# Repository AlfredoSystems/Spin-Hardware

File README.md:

# Spin-Hardware
Control system PCB files for The Greatest Danger and The Greatest Challenge. This Repo includes KiCAD projects for two boards, "Spin-Sonic" and "Spin-Eggman". "Spin-Sonic" is the main control board with RF, sensing, and the main MCU. "Spin-Eggman" is a power distribution board used to compactly mount the main switch, bulk capacitors, and battery connectors.

> ⚠️ While it's cool with us, I don't recommend anyone reproduce these exact boards. Learn more at the bottom of this page.

## Spin-Sonic Features
* Main MCU STM32F405RGT6 has FPU and high clock speed.
* 400g H3LIS331DL Accelerometer is rotated 45 degrees for increased precision.
* SX1276 915MHz LoRa transceiver circuit provides reliable wireless communication.
* SY8253ADC switching regulator provides up to 3A at 3.3V. Maximum input voltage of 23V. 
* TRRS jack provides swift and robust Serial Wire Debug (SWD) programming interface

## Why you shouldn't make one of these
1. The LoRa wireless system is put together pretty much from scratch. They don't really sell handheld LoRa transmitters. We made one ourselves, a process I do not recommend to anyone. We also have to make the antenna for each board.
2. Spin-Sonic was designed to be assembled by JLCPCB, unfortunately JLC does not stock 400g accelerometers. H3LIS331DL's had to be soldered after the fact, a process that can be tedious and unreliable.
3. Using a TRRS connector (audio jack) for the programming interface does make rapid code testing easier, but we did have to make a custom programming cable which was a pain.

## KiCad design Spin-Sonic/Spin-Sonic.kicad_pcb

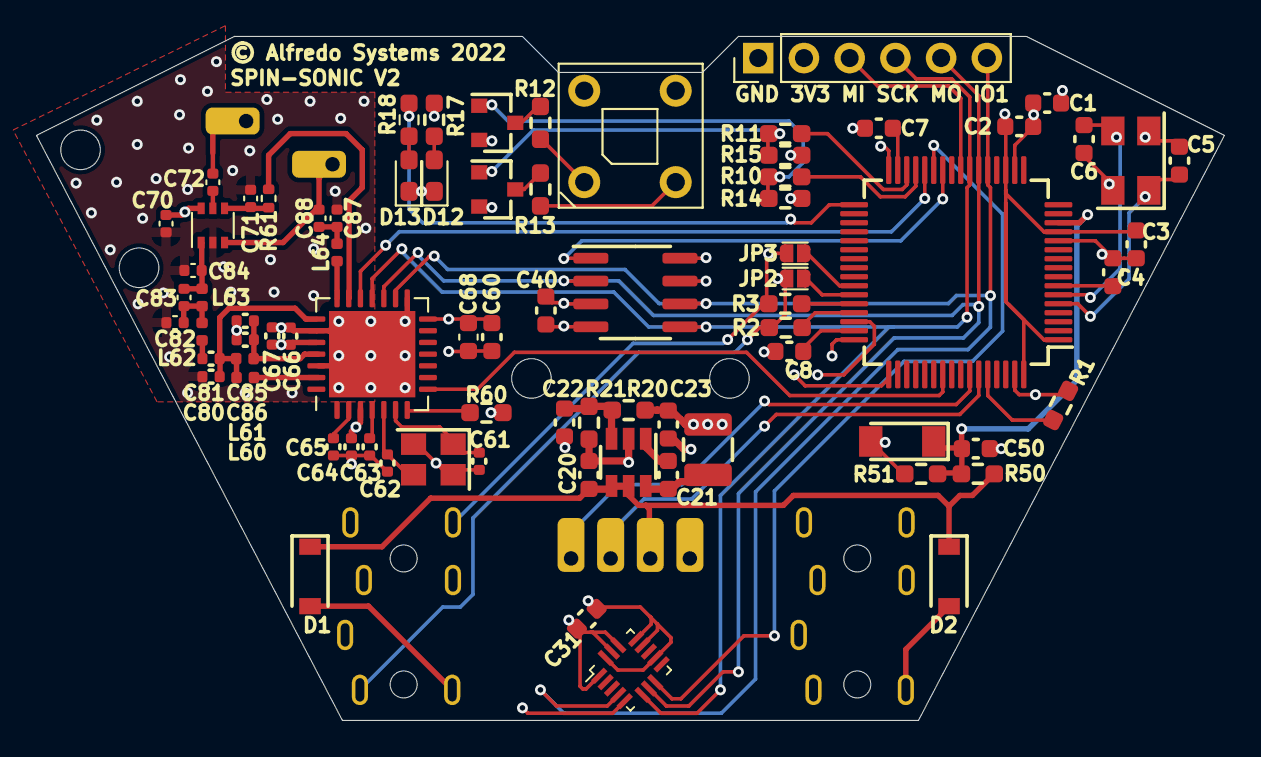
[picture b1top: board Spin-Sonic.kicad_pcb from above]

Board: 4 copper layers, 66.0 x 38.0 mm, 86 parts (0 on the bottom side), 62 nets.

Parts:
C1, C7, C8, C20, C60: 2.2uF; C_0603_1608Metric
C2, C3, C4, C21, C31, C40, C50, C68: 100nF; C_0603_1608Metric
C5, C6: 15pF; C_0603_1608Metric
C22: 22pF; C_0603_1608Metric
C23: 22uF; C_0603_1608Metric
C61, C62: 15pF; C_0402_1005Metric
C63, C64, C65, C67, C85: 100nF; C_0402_1005Metric
C66, C72, C86, C88: 47pF; C_0402_1005Metric
C70, C71: 1nF; C_0402_1005Metric
C80, C82: 8.2pF; C_0402_1005Metric
C81: 22pF; C_0402_1005Metric
C83: 1.5pF; C_0402_1005Metric
C84, C87: 3.3pF; C_0402_1005Metric
D1, D2: B5819W; D_SOD-123
D10: R50RB2-F-0160
D12: LED_3V3; LED_0603_1608Metric_Pad1.05x0.95mm_HandSolder
D13: LED_MISC; LED_0603_1608Metric_Pad1.05x0.95mm_HandSolder
D50: ZMM3V3; D_MiniMELF
J1, J2: G-Switch-ST-0322; G-Switch-ST-TRRS
J4, J5, J6, J7: Conn_01x01; TGD-antenna-THT
J8: Conn_01x06; PinHeader_1x06_P2.54mm_Vertical
J64, J65: Conn_01x01_Female; TGD-antenna-THT
JP2, JP3: SolderJumper_2_Open; TGD_SolderJumper
L20: 4.7uH; L_1210_3225Metric
L60: 2.2nH; L_0402_1005Metric
L61: 33nH; L_0402_1005Metric
L62: 5.6nH; L_0402_1005Metric
L63: 4.7nH; L_0402_1005Metric
L64: 10nH; L_0402_1005Metric
Q11, Q12: AO3401A; SOT-23
R1, R14, R15, R20, R60: 10K; R_0603_1608Metric_Pad0.98x0.95mm_HandSolder
R2, R3, R13: 22R; R_0603_1608Metric_Pad0.98x0.95mm_HandSolder
R10, R11, R17, R18: 1K; R_0603_1608Metric_Pad0.98x0.95mm_HandSolder
R12: 10R; R_0603_1608Metric_Pad0.98x0.95mm_HandSolder
R21, R51: 2K2; R_0603_1608Metric_Pad0.98x0.95mm_HandSolder
R50: 15K; R_0603_1608Metric_Pad0.98x0.95mm_HandSolder
R61: 1K; R_0402_1005Metric
U1: STM32F405RGTx; LQFP-64_10x10mm_P0.5mm
U2: Crystal_GND24; Crystal_SMD_5032-4Pin_5.0x3.2mm
U20: SY8253ADC; TSOT-23-6
U30: H3LIS331DL; TGD-TFLGA-16_3x3mm
U40: LE25U40CMD; SOIC-8_3.9x4.9mm_P1.27mm
U60: SX1276; TGD-QFN-28-1EP_6x6mm_P0.65mm_EP4.8x4.8mm
U61: Crystal_GND24; Crystal_SMD_3225-4Pin_3.2x2.5mm
U62: PE4259; SOT-363_SC-70-6

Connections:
+3V3: C1.1, C2.1, C3.1, C22.1, C23.1, C31.1, C40.1, C60.1, C64.1, C66.1, C67.1, C68.1, C70.2, J8.2, L20.2, Q11.2 (S), Q12.2 (S), R14.1, R15.1, R17.1, R20.1, R60.1, U1.1 (VBAT), U1.13 (VDDA), U1.19 (VDD), U1.32 (VDD), U1.48 (VDD), U1.64 (VDD), U30.1 (VDDIO), U30.14 (VDD), U30.15 (VDDR), U40.3 (WP), U40.7 (HOLD), U40.8 (VDD), U60.3 (VBAT_ANA_1), U60.14 (VBAT_DIG_3), U60.24 (VBAT_RF_2), U62.6 (VDD)
/sx1276/Antenna: C72.2, J65.1
/sx1276/RST: R60.2, U60.7 (NRESET)
CS_A: U1.27 (PB1), U30.8 (CS)
CS_L: U1.28 (PB2), U60.19 (~CS)
CS_M: U1.26 (PB0), U40.1 (CS)
GND: C1.2, C2.2, C3.2, C4.1, C5.1, C6.1, C7.2, C8.2, C20.2, C23.2, C31.2, C40.2, C50.2, C60.2, C61.1, C62.1, C63.2, C64.2, C65.2, C66.2, C67.2, C68.2, C70.1, C71.1, C80.2, C82.2, C84.2, C85.2, C86.2, C87.2, D10.1 (NC), D10.2 (COM_CA), D12.1 (K), D13.1 (K), D50.2 (A), J1.4 (Audio_L), J2.4 (Audio_L), J7.1, J8.1, R1.1, R21.2, R51.2, U1.12 (VSSA), U1.18 (VSS), U1.63 (VSS), U2.2, U2.4, U20.2 (GND), U30.5 (GND), U30.10 (GNDR), U30.12 (GND), U30.13 (GND), U30.16 (GND), U40.4 (VSS), U60.15 (GND), U60.23 (GND), U60.26 (GND), U60.29 (GND_PAD), U61.2, U61.4, U62.2 (GND)
GPIO1: J8.3, U1.24 (PC4)
INT_L: U1.55 (PB3), U60.8 (DIO0)
LED_BLUE: R10.1, U1.29 (PB10)
LED_MISC: R18.1, U1.33 (PB12)
LED_RED: R11.1, U1.30 (PB11)
unnamed: C4.2, U1.7 (NRST)
unnamed: C5.2, U1.5 (PH0), U2.1
unnamed: C6.2, U1.6 (PH1), U2.3
unnamed: C7.1, U1.31 (VCAP_1)
unnamed: C8.1, U1.47 (VCAP_2)
unnamed: C21.1, U20.1 (BS)
unnamed: C21.2, L20.1, U20.6 (LX)
unnamed: C22.2, R20.2, R21.1, U20.3 (FB)
unnamed: C61.2, U60.6 (XTB), U61.1
unnamed: C62.2, U60.5 (XTA), U61.3
unnamed: C63.1, U60.4 (VR_DIG)
unnamed: C65.1, U60.2 (VR_ANA)
unnamed: C71.2, R61.1, U62.4 (CTRL)
unnamed: C72.1, U62.5 (RFC)
unnamed: C81.2, L62.1
unnamed: C82.1, C83.1, L62.2, L63.1
unnamed: C87.1, C88.2, L64.2
unnamed: D1.2 (A), J1.1 (GND)
unnamed: D2.2 (A), J2.1 (GND)
unnamed: D10.3 (BLUE_AN), R12.2
unnamed: D10.4 (RED_AN), R13.2
unnamed: D12.2 (A), R17.2
unnamed: D13.2 (A), R18.2
unnamed: J1.2 (MIC), JP2.1 (A), R2.2
unnamed: J1.3 (Audio_R), JP3.1 (A), R3.1
unnamed: Q11.1 (G), R10.2, R14.2
unnamed: Q11.3 (D), R12.1
unnamed: Q12.1 (G), R11.2, R15.2
unnamed: Q12.3 (D), R13.1
unnamed: R1.2, U1.60 (BOOT0)
PA_BOOST: L60.1, U60.27 (PA_BOOST)
PPM_B: J5.1, U1.59 (PB7)
PPM_F: J4.1, U1.58 (PB6)
P_MISO: J8.5, U1.22 (PA6), U30.7 (MISO), U40.2 (SO/SIO1), U60.17 (MISO)
P_MOSI: J8.4, U1.23 (PA7), U30.6 (MOSI), U40.5 (SI/SIO0), U60.18 (MOSI)
P_SCK: J8.6, U1.21 (PA5), U30.4 (SCK), U40.6 (SCK), U60.16 (SCK)
RF1: C83.2, C84.1, L63.2, U62.1 (RF1)
RF2: C88.1, J64.1, U62.3 (RF2)
RFI_HF: L64.1, U60.21 (RFI_HF)
RFO_HF: C80.1, C81.1, L60.2, L61.1, U60.22 (RFO_HF)
RF_MOD: R61.2, U60.20 (RF_MOD)
SNS_VIN: C50.1, D50.1 (K), R50.2, R51.1, U1.14 (PA0)
SWD_CLK: J2.3 (Audio_R), U1.49 (PA14)
SWD_DIO: J2.2 (MIC), U1.46 (PA13)
USB_DM: R3.2, U1.44 (PA11)
USB_DP: R2.1, U1.45 (PA12)
USB_RX: JP2.2 (B), U1.43 (PA10)
USB_TX: JP3.2 (B), U1.42 (PA9)
VDD: C20.1, D1.1 (K), D2.1 (K), J6.1, R50.1, U20.4 (EN), U20.5 (IN)
VR_PA: C85.1, C86.1, L61.2, U60.25 (VR_PA)

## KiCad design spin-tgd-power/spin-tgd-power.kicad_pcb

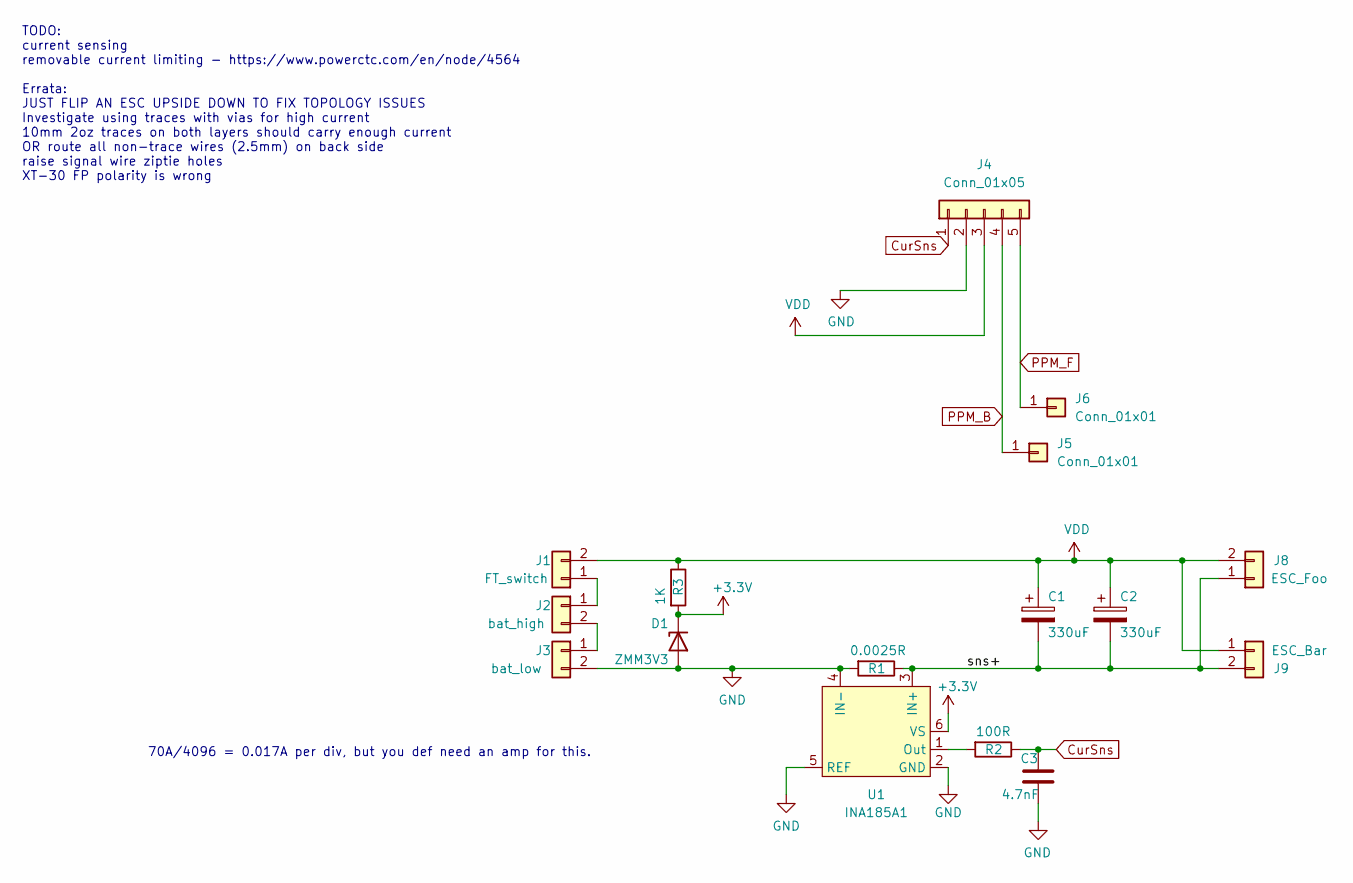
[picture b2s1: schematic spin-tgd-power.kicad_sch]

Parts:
C1, C2: 330uF; TGD_lowESR_cap
C3: 4.7nF; C_0603_1608Metric; LCSC C53987
D1: ZMM3V3; D_MiniMELF; LCSC C8056
J1: FT_switch; FT_Switch_Vertical
J2: bat_high; TGD_2P_BatHoles
J3: bat_low; TGD_2P_BatHoles
J4: Conn_01x05; JST_EH_B5B-EH-A_1x05_P2.50mm_Vertical
J5, J6: Conn_01x01; TGD-antenna-THT
J8: ESC_Foo; TGD_ESC_SigPads
J9: ESC_Bar; TGD_ESC_SigPads
R1: 0.0025R; R_2512_6332Metric_Pad1.40x3.35mm_HandSolder
R2: 100R; R_0603_1608Metric; LCSC C22775
R3: 1K; R_0603_1608Metric
U1: INA185A1; SOT-563

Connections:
+3V3: D1.1 (K), R3.2, U1.6 (VS)
/sns+: C1.2, C2.2, J8.1, J9.2, R1.1, U1.3 (IN+)
CurSns: C3.2, J4.1, R2.1
GND: C3.1, D1.2 (A), J3.2, J4.2, R1.2, U1.2 (GND), U1.4 (IN-), U1.5 (REF)
unnamed: J1.1, J2.1
unnamed: J2.2, J3.1
unnamed: R2.2, U1.1 (Out)
PPM_B: J4.4, J5.1
PPM_F: J4.5, J6.1
VDD: C1.1, C2.1, J1.2, J4.3, J8.2, J9.1, R3.1

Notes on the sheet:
70A/4096 = 0.017A per div, but you def need an amp for this.
TODO: current sensing removable current limiting - https://www.powerctc.com/en/node/4564 Errata: JUST FLIP AN ESC UPSIDE DOWN TO FIX TOPOLOGY ISSUES Investigate using traces with vias for high current 10mm 2oz traces on both layers should carry enough current OR route all non-trace wires (2.5mm) on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

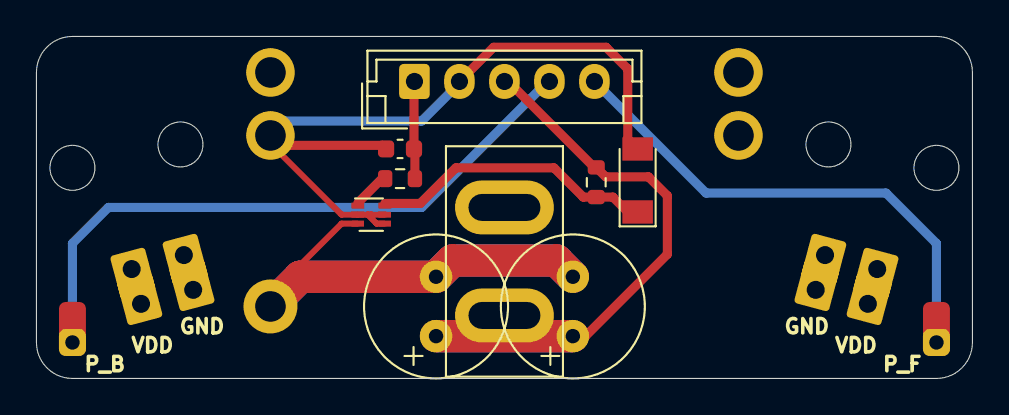
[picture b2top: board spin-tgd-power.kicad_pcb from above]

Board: 2 copper layers, 52.0 x 19.0 mm, 16 parts (1 on the bottom side), 10 nets.

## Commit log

2022-01-02 Initial revision, used at NHRL Nov21
2022-01-02 added pull-up resistors for LED FETS
2022-01-08 Schematic and Layout first draft completed, need to route next
2022-01-13 last V2 version before switching to separate power and control boards
2022-01-16 Version of both power and control boards ordered on 1-15-21
2022-01-24 DSP DAC circuit and FO card todo notes
2022-05-08 Moved to new library system
2022-05-10 Added .gitignore
2022-05-12 created pdfs for V2 schematics
2022-05-31 Eggman V2 ordered gerbers
2022-10-20 file cleanup
2022-10-20 Capitalized filenames + renamed project
2022-10-20 added electronics image
2022-10-20 added image to readme
2022-10-20 more readme updates
2022-10-21 extended readme
2022-10-21 added PCB image
2022-10-21 made images smaller
2022-10-21 fixed typos
2022-10-21 fixed images
2022-10-21 minor edits
2022-10-21 added image folder and Spin-Sonic PDF
2022-10-21 updated image loactions
2022-10-21 removed project files
2022-10-21 updated schematic descriptions
2022-10-21 added a simple license
2022-10-21 updated warning
2022-11-14 minor readme edits
2022-11-26 updated gitignore

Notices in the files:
Spin-Sonic/Spin-Sonic.kicad_pcb:
© Alfredo Systems 2022
spin-tgd-power/spin-tgd-power.kicad_pcb:
© Jacob Williams 2022
